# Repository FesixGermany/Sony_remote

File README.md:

I wanted a remote control for my Sony a6500 camera which has an IR receiver. There is a dedicated remote control with tons of buttons I don't need so I thought this would be a nice little project as all I need is a button for instant action and for a two second delay.  
Additionally the command for starting and stopping video recording is in the firmware so the functionality of the buttons can be changed.  
Exchange `ShutterCode` or `TwoSecsCode` with `VideoCode`.

```c
#define ButtonRightCode ShutterCode
#define ButtonLeftCode	TwoSecsCode
```

The whole circuit is powered by a 2032 button cell.  
The controller generates the necessary 40kHz modulation and sends the command set in the firmware when the button is pressed. As long as the command is transmitted the green LED is lit.
After that the controller goes into sleep mode to save battery.

In order to work with the camera the remote function needs to be enabled in the system menu.

The original code is from http://www.technoblogy.com/show?VFT

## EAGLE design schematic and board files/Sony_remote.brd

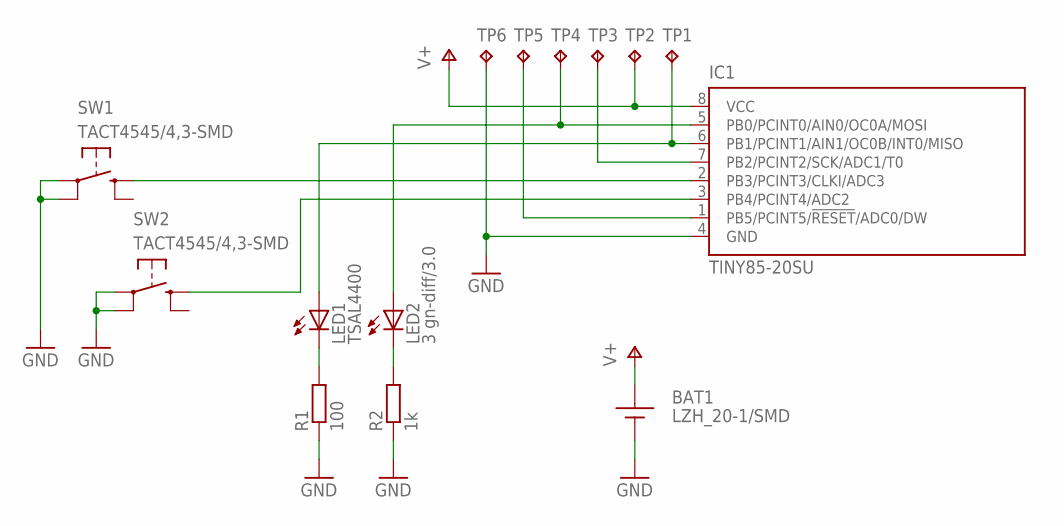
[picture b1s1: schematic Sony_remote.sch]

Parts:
BAT1: LZH_20-1/SMD
IC1: TINY85-20SU; 8S2
LED1: TSAL4400; LED3MM
LED2: 3 gn-diff/3.0; LED3MM
R1: 100; M0805
R2: 1k; M0805
SW1, SW2: TACT4545/4,3-SMD; TACT4545-SMD
TP1: MISO; B1,27
TP2: VCC; B1,27
TP3: SCK; B1,27
TP4: MOSI; B1,27
TP5: RST; B1,27
TP6: GND; B1,27

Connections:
GND: BAT1.-, IC1.4 (GND), R1.1, R2.1, SW1.P$1, SW1.P$2 (P1), SW2.P$1, SW2.P$2 (P1), TP6.TP
unnamed: IC1.2 (PB3/PCINT3/CLKI/ADC3), SW1.P$3 (S)
unnamed: IC1.7 (PB2/PCINT2/SCK/ADC1/T0), TP3.TP
unnamed: IC1.3 (PB4/PCINT4/ADC2), SW2.P$3 (S)
unnamed: IC1.5 (PB0/PCINT0/AIN0/OC0A/MOSI), LED2.A, TP4.TP
unnamed: IC1.6 (PB1/PCINT1/AIN1/OC0B/INT0/MISO), LED1.A, TP1.TP
unnamed: IC1.1 (PB5/PCINT5/!RESET!/ADC0/DW), TP5.TP
unnamed: LED1.K (C), R1.2
unnamed: LED2.K (C), R2.2
V+: BAT1.+, IC1.8 (VCC), TP2.TP

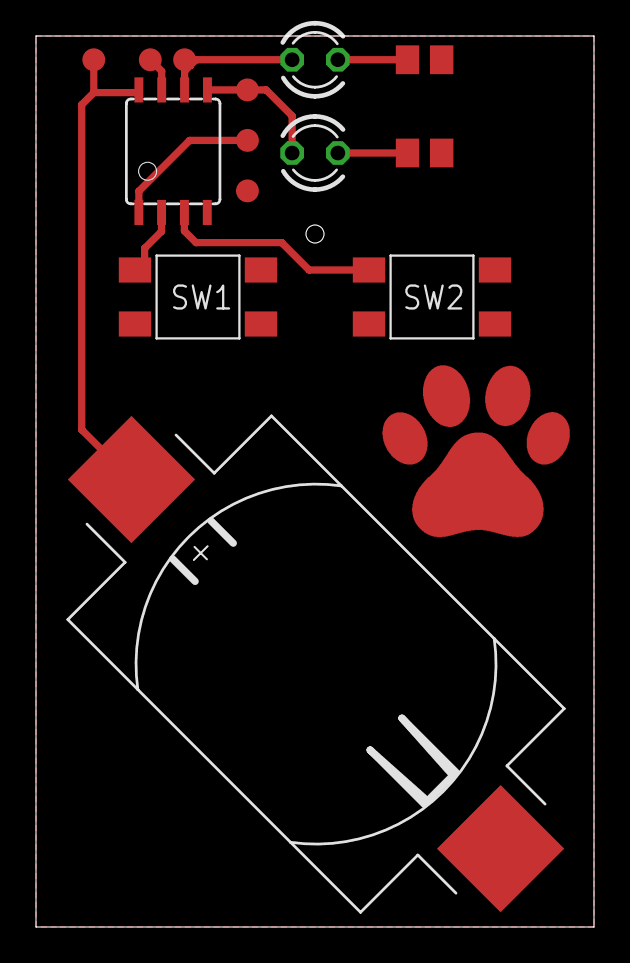
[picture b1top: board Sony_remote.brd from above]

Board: 2 copper layers, 31.0 x 49.5 mm, 14 parts (0 on the bottom side), 10 nets.

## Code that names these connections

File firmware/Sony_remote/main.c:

/*
 * ATtiny85 Sony NEX/Alpha Remote Control
 *
 * David Johnson-Davies - www.technoblogy.com - 12th April 2015
 * ATtiny85 @ 1 MHz (internal oscillator; BOD disabled)
 *
 * CC BY 4.0
 * Licensed under a Creative Commons Attribution 4.0 International license: 
 * http://creativecommons.org/licenses/by/4.0/
 *
 * 
 * Modified by Fesix
 * Converted from Arduino C to standard AVR C, some formatting of code and comments added.
 * Original code had a third button on PB5 for video, change defines as needed for functionality of buttons.
 * 
 * Original source: http://www.technoblogy.com/show?VFT
 *
 * Note: IR LED stays lit until one button is pressed the first time.
 *
 */ 

#include <avr/io.h>
#include <avr/sleep.h>
#include <avr/interrupt.h>

// Pin assignments
#define IRout 			PB1   // OC0B
#define ButtonRight		PB4
#define ButtonLeft		PB3
#define LED 			PB0

// Assign button functions, look next segment 'Remote Control' and replace as needed
#define ButtonRightCode ShutterCode
#define ButtonLeftCode	TwoSecsCode

// Remote control
const int Address = 0x1E3A;		// Destination of code
const int ShutterCode = 0x2D;	// Activate shutter without delay
const int TwoSecsCode = 0x37;	// Activate shutter with two second delay
const int VideoCode = 0x48;		// Start video recording

// IR transmitter *****************************************

const int top = 24;    // 1000000/25 = 40kHz
const int match = 18;  // pulses with approx 25% mark/space ratio

// Set up Timer/Counter0 to output PCM on OC0B
void SetupPCM ()
{
	TCCR0A |= (3 << COM0B0) | (3 << WGM00);				// Inverted output on OC0B and Fast PWM
	TCCR0B |= (1 << WGM02) | (1 << CS00);				// Fast PWM and divide by 1
	OCR0A = top;										// 40kHz
	OCR0B = top;										// Keep output low
}

// Set up pin change interrupts on button pins
void SetupPinChange ()
{
	PCMSK |= (1 << ButtonRight) | (1 << ButtonLeft);	// Pin change mask register
	GIMSK |= (1 << PCIE);								// Pin change interrupt enable
}

void Pulse (int carrier, int gap)
{
	int count = carrier;								// First send carrier pulses
	OCR0B = match;										// Generate pulses
	for (char i = 0; i < 2; i++)
	{
		for (int c = 0; c < count; c++)
		{
			do ; while ((TIFR & (1 << TOV0)) == 0);		// Counter0 overflow flag
			TIFR |= (1 << TOV0);
		}
		count = gap;									// Now send no pulses (gap)
		OCR0B = top;									// Output low because OCR0B equals OCR0A
	}
}

void SendSony (unsigned long code)
{
	TCNT0 = 0;											// Start counting from 0
	// Send Start pulse
	Pulse (96, 24);
	// Send 20 bits
	for (int Bit = 0; Bit < 20; Bit++)
	{
		if (code & ((unsigned long) 1<<Bit))			// If bit of code is 1
			Pulse (48, 24);
		else Pulse (24, 24);							// If bit of code is 0
	}
}

// Transmit code and light LED
void Transmit (int address, int command)
{
	unsigned long code = (unsigned long) address << 7 | command;	// Join address and command
	PORTB |= (1 << LED);								// Control LED on begin transmit
	SendSony (code);									// Send code
	Pulse (0, 430);										// Wait 11ms and send again (430*25us)
	SendSony (code);
	Pulse (0, 430);										// Wait 11ms and send again (430*25us)
	SendSony (code);
	PORTB &= ~(1 << LED);								// Control LED off transmit complete
}

// Interrupt **********************************************

// Use PCINT0 just to wake up from sleep
ISR (PCINT0_vect)
{
}

 
 // Main program ******************************************
 
 int main (void)
 {
	 DDRB &= ~(1 << ButtonRight) | ~(1 << ButtonLeft);	// Inputs
	 PORTB |= (1 << ButtonRight) | (1 << ButtonLeft) ;	// Internal pullups for buttons
	 DDRB |= (1 << IRout) | (1 << LED);					// Outputs
	 
	 set_sleep_mode(SLEEP_MODE_PWR_DOWN);				// MCUCR |= (1 << SM1);
	 
	 ADCSRA &= ~(1<<ADEN);								// Disable ADC to save power
	 
	 SetupPCM(); 
	 SetupPinChange();
	 
	 // Main loop
	 while (1)
	 {
		// Go to sleep
		sleep_enable();									// Equals MCUCR |= (1 << SE);
		sei();
		sleep_cpu();
		
		// Come here after pin change interrupt wakes us from sleep
		// Check which button is pressed and transmit
		if (!(PINB & (1 << ButtonRight)))
			Transmit (Address, ShutterCode);
		else if (!(PINB & (1 << ButtonLeft)))
			Transmit (Address, TwoSecsCode);
		// Wait for all buttons to be released
		do ; while (!(PINB & (1 << ButtonRight)) || !(PINB & (1 << ButtonLeft)));
	}
}
